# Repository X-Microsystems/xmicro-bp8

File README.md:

# XMICRO-BP8

Eight-slot [XMICRO](https://github.com/x-microsystems/xmicro-bus) backplane.

Datasheet: [XMICRO-BP8](Documentation/XMICRO-BP8.pdf)

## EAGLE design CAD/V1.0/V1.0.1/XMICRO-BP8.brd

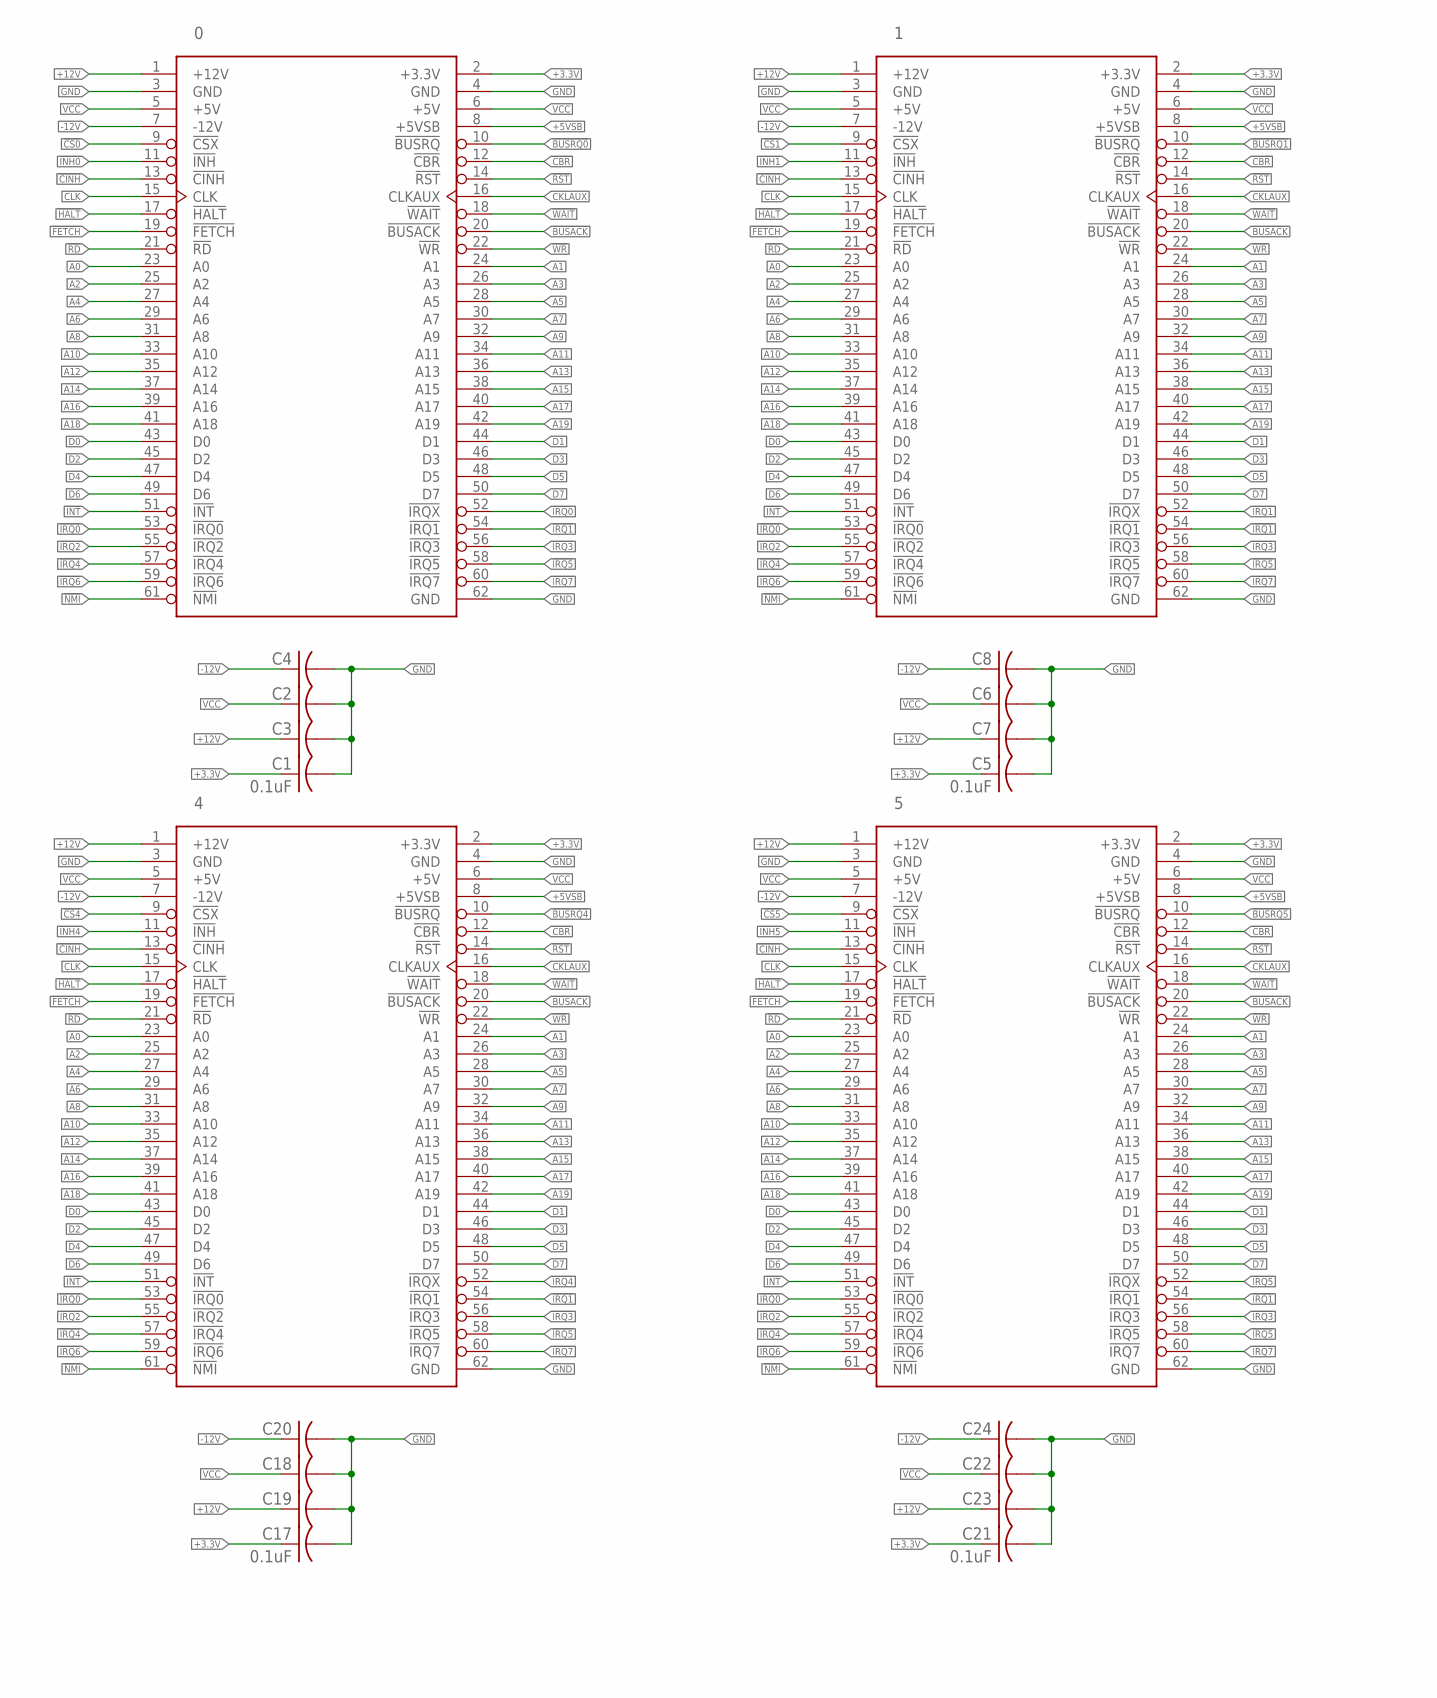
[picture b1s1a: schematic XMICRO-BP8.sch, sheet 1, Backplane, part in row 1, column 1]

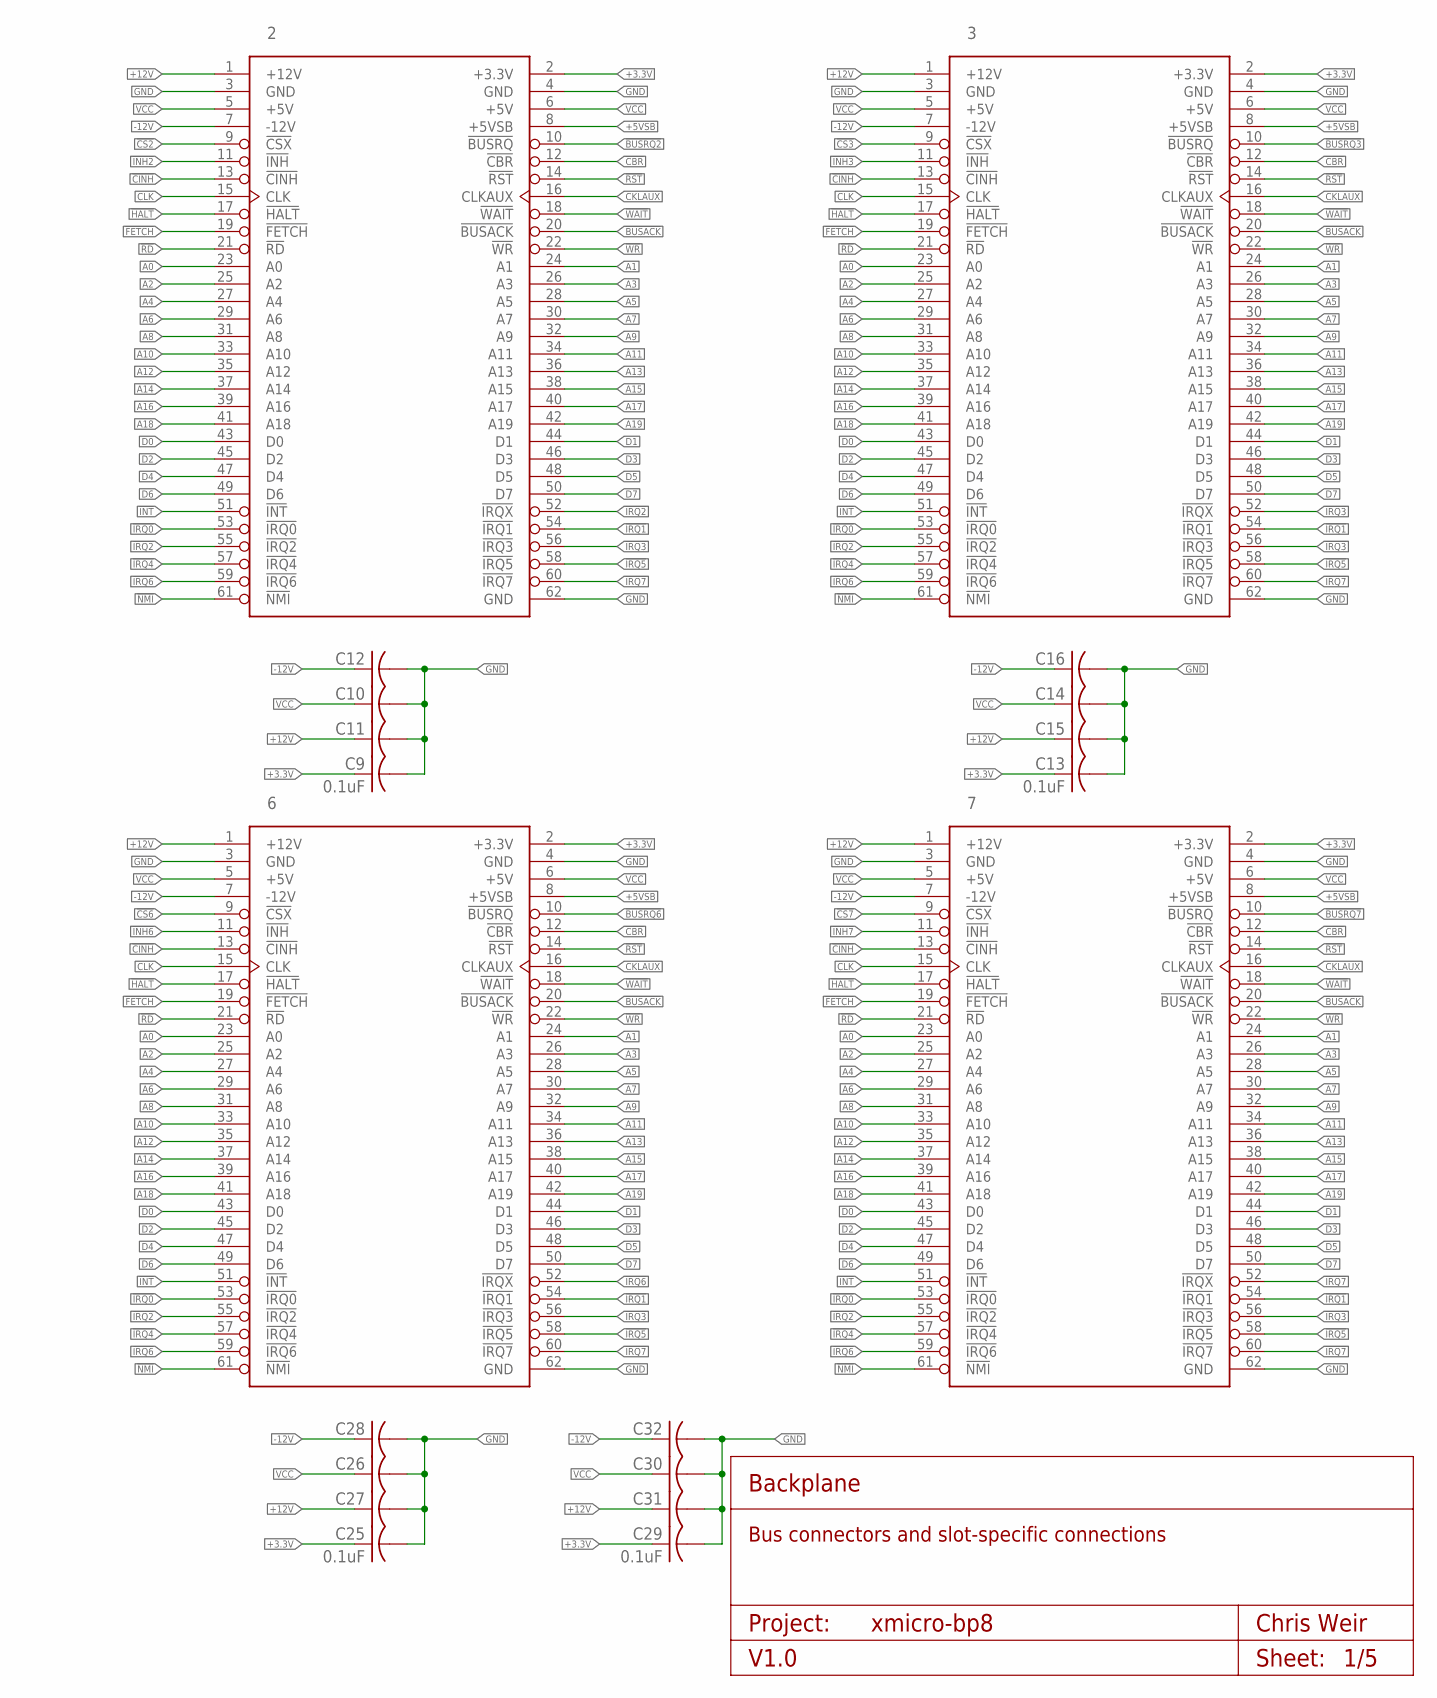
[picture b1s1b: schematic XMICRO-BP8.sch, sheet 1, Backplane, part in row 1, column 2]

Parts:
0, 1, 2, 3, 4, 5, 6, 7: XMICRO-BUS-PHYSICAL-EDGE62F; EDGE62F
C1, C2, C3, C5, C6, C7, C9, C10, C11, C13, C14, C15, C17, C18, C19, C21, C22, C23, C25, C26, C27, C29, C30, C31, C32: 0.1uF; C025-024X044
C4, C8, C12, C16, C20, C24, C28: 0.1uF; C050-024X044

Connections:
!BUSACK: 0.20 (!BUSACK), 1.20 (!BUSACK), 2.20 (!BUSACK), 3.20 (!BUSACK), 4.20 (!BUSACK), 5.20 (!BUSACK), 6.20 (!BUSACK), 7.20 (!BUSACK); also elsewhere on the board
!BUSRQ0: 0.10 (!BUSRQ); also elsewhere on the board
!BUSRQ1: 1.10 (!BUSRQ); also elsewhere on the board
!BUSRQ2: 2.10 (!BUSRQ); also elsewhere on the board
!BUSRQ3: 3.10 (!BUSRQ); also elsewhere on the board
!BUSRQ4: 4.10 (!BUSRQ); also elsewhere on the board
!BUSRQ5: 5.10 (!BUSRQ); also elsewhere on the board
!BUSRQ6: 6.10 (!BUSRQ); also elsewhere on the board
!BUSRQ7: 7.10 (!BUSRQ); also elsewhere on the board
!CBR: 0.12 (!CBR), 1.12 (!CBR), 2.12 (!CBR), 3.12 (!CBR), 4.12 (!CBR), 5.12 (!CBR), 6.12 (!CBR), 7.12 (!CBR); also elsewhere on the board
!CINH: 0.13 (!CINH), 1.13 (!CINH), 2.13 (!CINH), 3.13 (!CINH), 4.13 (!CINH), 5.13 (!CINH), 6.13 (!CINH), 7.13 (!CINH); also elsewhere on the board
!CS0: 0.9 (!CSX); also elsewhere on the board
!CS1: 1.9 (!CSX); also elsewhere on the board
!CS2: 2.9 (!CSX); also elsewhere on the board
!CS3: 3.9 (!CSX); also elsewhere on the board
!CS4: 4.9 (!CSX); also elsewhere on the board
!CS5: 5.9 (!CSX); also elsewhere on the board
!CS6: 6.9 (!CSX); also elsewhere on the board
!CS7: 7.9 (!CSX); also elsewhere on the board
!FETCH: 0.19 (!FETCH), 1.19 (!FETCH), 2.19 (!FETCH), 3.19 (!FETCH), 4.19 (!FETCH), 5.19 (!FETCH), 6.19 (!FETCH), 7.19 (!FETCH); also elsewhere on the board
!HALT: 0.17 (!HALT), 1.17 (!HALT), 2.17 (!HALT), 3.17 (!HALT), 4.17 (!HALT), 5.17 (!HALT), 6.17 (!HALT), 7.17 (!HALT); also elsewhere on the board
!INH0: 0.11 (!INH); also elsewhere on the board
!INH1: 1.11 (!INH); also elsewhere on the board
!INH2: 2.11 (!INH); also elsewhere on the board
!INH3: 3.11 (!INH); also elsewhere on the board
!INH4: 4.11 (!INH); also elsewhere on the board
!INH5: 5.11 (!INH); also elsewhere on the board
!INH6: 6.11 (!INH); also elsewhere on the board
!INH7: 7.11 (!INH); also elsewhere on the board
!INT: 0.51 (!INT), 1.51 (!INT), 2.51 (!INT), 3.51 (!INT), 4.51 (!INT), 5.51 (!INT), 6.51 (!INT), 7.51 (!INT); also elsewhere on the board
!IRQ0: 0.52 (!IRQX), 0.53 (!IRQ0), 1.53 (!IRQ0), 2.53 (!IRQ0), 3.53 (!IRQ0), 4.53 (!IRQ0), 5.53 (!IRQ0), 6.53 (!IRQ0), 7.53 (!IRQ0); also elsewhere on the board
!IRQ1: 0.54 (!IRQ1), 1.52 (!IRQX), 1.54 (!IRQ1), 2.54 (!IRQ1), 3.54 (!IRQ1), 4.54 (!IRQ1), 5.54 (!IRQ1), 6.54 (!IRQ1), 7.54 (!IRQ1); also elsewhere on the board
!IRQ2: 0.55 (!IRQ2), 1.55 (!IRQ2), 2.52 (!IRQX), 2.55 (!IRQ2), 3.55 (!IRQ2), 4.55 (!IRQ2), 5.55 (!IRQ2), 6.55 (!IRQ2), 7.55 (!IRQ2); also elsewhere on the board
!IRQ3: 0.56 (!IRQ3), 1.56 (!IRQ3), 2.56 (!IRQ3), 3.52 (!IRQX), 3.56 (!IRQ3), 4.56 (!IRQ3), 5.56 (!IRQ3), 6.56 (!IRQ3), 7.56 (!IRQ3); also elsewhere on the board
!IRQ4: 0.57 (!IRQ4), 1.57 (!IRQ4), 2.57 (!IRQ4), 3.57 (!IRQ4), 4.52 (!IRQX), 4.57 (!IRQ4), 5.57 (!IRQ4), 6.57 (!IRQ4), 7.57 (!IRQ4); also elsewhere on the board
!IRQ5: 0.58 (!IRQ5), 1.58 (!IRQ5), 2.58 (!IRQ5), 3.58 (!IRQ5), 4.58 (!IRQ5), 5.52 (!IRQX), 5.58 (!IRQ5), 6.58 (!IRQ5), 7.58 (!IRQ5); also elsewhere on the board
!IRQ6: 0.59 (!IRQ6), 1.59 (!IRQ6), 2.59 (!IRQ6), 3.59 (!IRQ6), 4.59 (!IRQ6), 5.59 (!IRQ6), 6.52 (!IRQX), 6.59 (!IRQ6), 7.59 (!IRQ6); also elsewhere on the board
!IRQ7: 0.60 (!IRQ7), 1.60 (!IRQ7), 2.60 (!IRQ7), 3.60 (!IRQ7), 4.60 (!IRQ7), 5.60 (!IRQ7), 6.60 (!IRQ7), 7.52 (!IRQX), 7.60 (!IRQ7); also elsewhere on the board
!NMI: 0.61 (!NMI), 1.61 (!NMI), 2.61 (!NMI), 3.61 (!NMI), 4.61 (!NMI), 5.61 (!NMI), 6.61 (!NMI), 7.61 (!NMI); also elsewhere on the board
!RD: 0.21 (!RD), 1.21 (!RD), 2.21 (!RD), 3.21 (!RD), 4.21 (!RD), 5.21 (!RD), 6.21 (!RD), 7.21 (!RD); also elsewhere on the board
!RST: 0.14 (!RST), 1.14 (!RST), 2.14 (!RST), 3.14 (!RST), 4.14 (!RST), 5.14 (!RST), 6.14 (!RST), 7.14 (!RST); also elsewhere on the board
!WAIT: 0.18 (!WAIT), 1.18 (!WAIT), 2.18 (!WAIT), 3.18 (!WAIT), 4.18 (!WAIT), 5.18 (!WAIT), 6.18 (!WAIT), 7.18 (!WAIT); also elsewhere on the board
!WR: 0.22 (!WR), 1.22 (!WR), 2.22 (!WR), 3.22 (!WR), 4.22 (!WR), 5.22 (!WR), 6.22 (!WR), 7.22 (!WR); also elsewhere on the board
+3.3V: 0.2 (+3.3V), 1.2 (+3.3V), 2.2 (+3.3V), 3.2 (+3.3V), 4.2 (+3.3V), 5.2 (+3.3V), 6.2 (+3.3V), 7.2 (+3.3V), C1.1, C5.1, C9.1, C13.1, C17.1, C21.1, C25.1, C29.1; also elsewhere on the board
+5VSB: 0.8 (+5VSB), 1.8 (+5VSB), 2.8 (+5VSB), 3.8 (+5VSB), 4.8 (+5VSB), 5.8 (+5VSB), 6.8 (+5VSB), 7.8 (+5VSB); also elsewhere on the board
+12V: 0.1 (+12V), 1.1 (+12V), 2.1 (+12V), 3.1 (+12V), 4.1 (+12V), 5.1 (+12V), 6.1 (+12V), 7.1 (+12V), C3.1, C7.1, C11.1, C15.1, C19.1, C23.1, C27.1, C31.1; also elsewhere on the board
A0: 0.23 (A0), 1.23 (A0), 2.23 (A0), 3.23 (A0), 4.23 (A0), 5.23 (A0), 6.23 (A0), 7.23 (A0); also elsewhere on the board
A1: 0.24 (A1), 1.24 (A1), 2.24 (A1), 3.24 (A1), 4.24 (A1), 5.24 (A1), 6.24 (A1), 7.24 (A1); also elsewhere on the board
A2: 0.25 (A2), 1.25 (A2), 2.25 (A2), 3.25 (A2), 4.25 (A2), 5.25 (A2), 6.25 (A2), 7.25 (A2); also elsewhere on the board
A3: 0.26 (A3), 1.26 (A3), 2.26 (A3), 3.26 (A3), 4.26 (A3), 5.26 (A3), 6.26 (A3), 7.26 (A3); also elsewhere on the board
A4: 0.27 (A4), 1.27 (A4), 2.27 (A4), 3.27 (A4), 4.27 (A4), 5.27 (A4), 6.27 (A4), 7.27 (A4); also elsewhere on the board
A5: 0.28 (A5), 1.28 (A5), 2.28 (A5), 3.28 (A5), 4.28 (A5), 5.28 (A5), 6.28 (A5), 7.28 (A5); also elsewhere on the board
A6: 0.29 (A6), 1.29 (A6), 2.29 (A6), 3.29 (A6), 4.29 (A6), 5.29 (A6), 6.29 (A6), 7.29 (A6); also elsewhere on the board
A7: 0.30 (A7), 1.30 (A7), 2.30 (A7), 3.30 (A7), 4.30 (A7), 5.30 (A7), 6.30 (A7), 7.30 (A7); also elsewhere on the board
A8: 0.31 (A8), 1.31 (A8), 2.31 (A8), 3.31 (A8), 4.31 (A8), 5.31 (A8), 6.31 (A8), 7.31 (A8); also elsewhere on the board
A9: 0.32 (A9), 1.32 (A9), 2.32 (A9), 3.32 (A9), 4.32 (A9), 5.32 (A9), 6.32 (A9), 7.32 (A9); also elsewhere on the board
A10: 0.33 (A10), 1.33 (A10), 2.33 (A10), 3.33 (A10), 4.33 (A10), 5.33 (A10), 6.33 (A10), 7.33 (A10); also elsewhere on the board
A11: 0.34 (A11), 1.34 (A11), 2.34 (A11), 3.34 (A11), 4.34 (A11), 5.34 (A11), 6.34 (A11), 7.34 (A11); also elsewhere on the board
A12: 0.35 (A12), 1.35 (A12), 2.35 (A12), 3.35 (A12), 4.35 (A12), 5.35 (A12), 6.35 (A12), 7.35 (A12); also elsewhere on the board
A13: 0.36 (A13), 1.36 (A13), 2.36 (A13), 3.36 (A13), 4.36 (A13), 5.36 (A13), 6.36 (A13), 7.36 (A13); also elsewhere on the board
A14: 0.37 (A14), 1.37 (A14), 2.37 (A14), 3.37 (A14), 4.37 (A14), 5.37 (A14), 6.37 (A14), 7.37 (A14); also elsewhere on the board
A15: 0.38 (A15), 1.38 (A15), 2.38 (A15), 3.38 (A15), 4.38 (A15), 5.38 (A15), 6.38 (A15), 7.38 (A15); also elsewhere on the board
A16: 0.39 (A16), 1.39 (A16), 2.39 (A16), 3.39 (A16), 4.39 (A16), 5.39 (A16), 6.39 (A16), 7.39 (A16); also elsewhere on the board
A17: 0.40 (A17), 1.40 (A17), 2.40 (A17), 3.40 (A17), 4.40 (A17), 5.40 (A17), 6.40 (A17), 7.40 (A17); also elsewhere on the board
A18: 0.41 (A18), 1.41 (A18), 2.41 (A18), 3.41 (A18), 4.41 (A18), 5.41 (A18), 6.41 (A18), 7.41 (A18); also elsewhere on the board
A19: 0.42 (A19), 1.42 (A19), 2.42 (A19), 3.42 (A19), 4.42 (A19), 5.42 (A19), 6.42 (A19), 7.42 (A19); also elsewhere on the board
CKLAUX: 0.16 (CLKAUX), 1.16 (CLKAUX), 2.16 (CLKAUX), 3.16 (CLKAUX), 4.16 (CLKAUX), 5.16 (CLKAUX), 6.16 (CLKAUX), 7.16 (CLKAUX); also elsewhere on the board
CLK: 0.15 (CLK), 1.15 (CLK), 2.15 (CLK), 3.15 (CLK), 4.15 (CLK), 5.15 (CLK), 6.15 (CLK), 7.15 (CLK); also elsewhere on the board
D0: 0.43 (D0), 1.43 (D0), 2.43 (D0), 3.43 (D0), 4.43 (D0), 5.43 (D0), 6.43 (D0), 7.43 (D0); also elsewhere on the board
D1: 0.44 (D1), 1.44 (D1), 2.44 (D1), 3.44 (D1), 4.44 (D1), 5.44 (D1), 6.44 (D1), 7.44 (D1); also elsewhere on the board
D2: 0.45 (D2), 1.45 (D2), 2.45 (D2), 3.45 (D2), 4.45 (D2), 5.45 (D2), 6.45 (D2), 7.45 (D2); also elsewhere on the board
D3: 0.46 (D3), 1.46 (D3), 2.46 (D3), 3.46 (D3), 4.46 (D3), 5.46 (D3), 6.46 (D3), 7.46 (D3); also elsewhere on the board
D4: 0.47 (D4), 1.47 (D4), 2.47 (D4), 3.47 (D4), 4.47 (D4), 5.47 (D4), 6.47 (D4), 7.47 (D4); also elsewhere on the board
D5: 0.48 (D5), 1.48 (D5), 2.48 (D5), 3.48 (D5), 4.48 (D5), 5.48 (D5), 6.48 (D5), 7.48 (D5); also elsewhere on the board
D6: 0.49 (D6), 1.49 (D6), 2.49 (D6), 3.49 (D6), 4.49 (D6), 5.49 (D6), 6.49 (D6), 7.49 (D6); also elsewhere on the board
D7: 0.50 (D7), 1.50 (D7), 2.50 (D7), 3.50 (D7), 4.50 (D7), 5.50 (D7), 6.50 (D7), 7.50 (D7); also elsewhere on the board
VCC: 0.5 (+5V), 0.6 (+5V), 1.5 (+5V), 1.6 (+5V), 2.5 (+5V), 2.6 (+5V), 3.5 (+5V), 3.6 (+5V), 4.5 (+5V), 4.6 (+5V), 5.5 (+5V), 5.6 (+5V), 6.5 (+5V), 6.6 (+5V), 7.5 (+5V), 7.6 (+5V), C2.1, C6.1, C10.1, C14.1, C18.1, C22.1, C26.1, C30.1; also elsewhere on the board

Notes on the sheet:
Backplane
Bus connectors and slot-specific connections
Project:
V1.0
Chris Weir
Sheet:

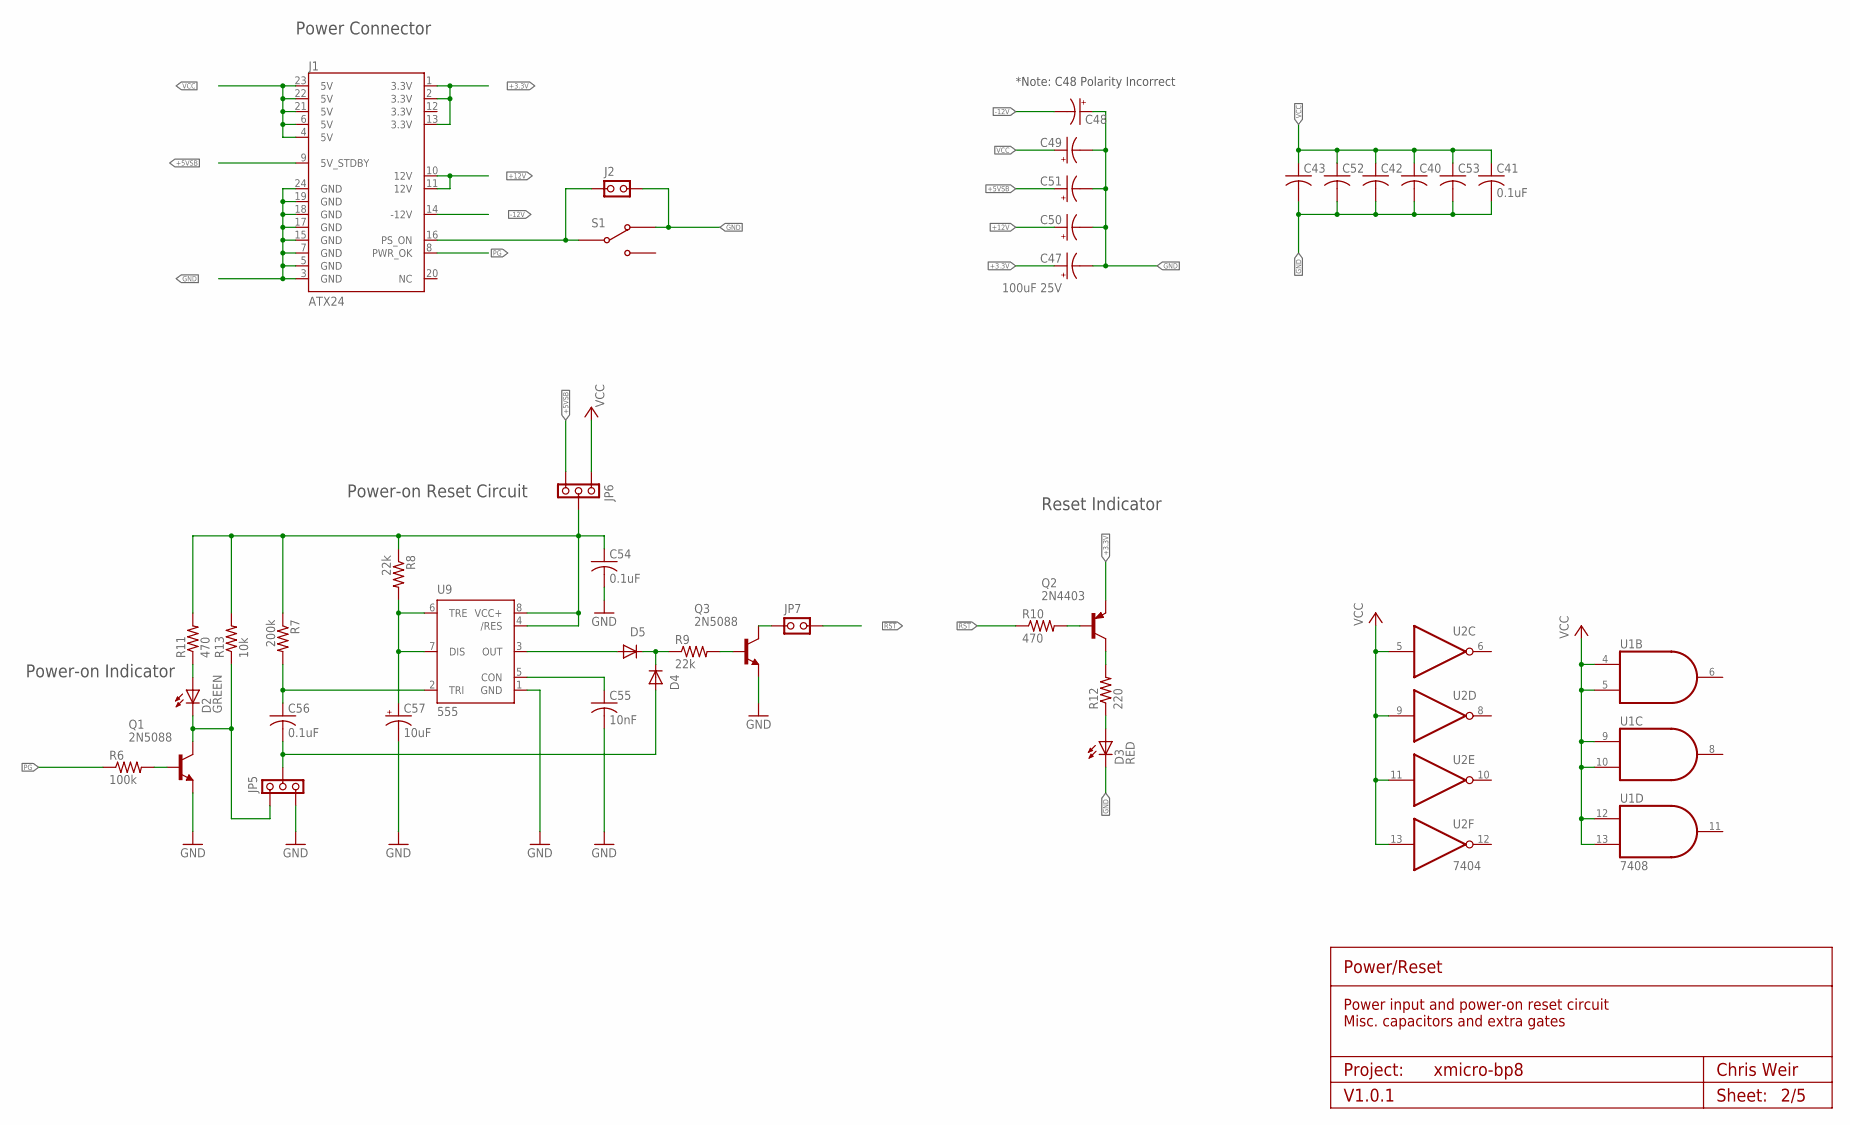
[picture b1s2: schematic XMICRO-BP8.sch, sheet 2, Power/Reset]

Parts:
C40, C41, C42, C43, C52, C53, C54, C56: 0.1uF; C025-024X044
C47, C50: 100uF 25V; C-10-5
C48, C49, C51: 220uF 10V; C-10-5
C55: 10nF; C025-024X044
C57: 10uF; E2,5-7
D2: GREEN; LED5MM
D3: RED; LED5MM
D4, D5: 1N4148DO35-7; DO35-7
J1: ATX24
J2: PINHD-1X2THRU; 1X02
JP5, JP6: PINHD1X3THRU; 1X03
JP7: PINHD-1X2THRU; 1X02
Q1, Q3: 2N5088; TO92
Q2: 2N4403; TO92
R6: 100k; 0207/10
R7: 200k; 0207/10
R8, R9: 22k; 0207/10
R10, R11: 470; 0207/10
R12: 220; 0207/10
R13: 10k; 0207/10
S1: SPDTT411013; T411013
U1: 7408; DIL14
U2: 7404; DIL14
U9: 555; DIL-08

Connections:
!RST: JP7.2, R10.1; also elsewhere on the board
+3.3V: C47.+, J1.1 (3.3V), J1.2 (3.3V), J1.13 (3.3V), Q2.1 (E); also elsewhere on the board
+5VSB: C51.+, J1.9 (5V_STDBY), JP6.3; also elsewhere on the board
+12V: C50.+, J1.10 (12V), J1.11 (12V); also elsewhere on the board
unnamed: D2.K (C), JP5.1, Q1.3 (C), R13.1
unnamed: Q2.3 (C), R12.2
unnamed: Q2.2 (B), R10.2
unnamed: D5.A, U9.3 (OUT)
unnamed: JP7.1, Q3.3 (C)
unnamed: D3.A, R12.1
unnamed: J1.16 (PS_ON), J2.1, S1.P$2
unnamed: Q1.2 (B), R6.2
unnamed: D2.A, R11.1
unnamed: C55.1, U9.5 (CON)
unnamed: D4.C, D5.C, R9.1
unnamed: C54.1, JP6.2, R7.1, R8.1, R11.2, R13.2, U9.4 (/RES), U9.8 (VCC+)
unnamed: C56.2, D4.A, JP5.2
unnamed: Q3.2 (B), R9.2
unnamed: C56.1, R7.2, U9.2 (TRI)
unnamed: C57.+, R8.2, U9.6 (TRE), U9.7 (DIS)
PG: J1.8 (PWR_OK), R6.1
VCC: C40.1, C41.1, C42.1, C43.1, C49.+, C52.1, C53.1, J1.4 (5V), J1.6 (5V), J1.21 (5V), J1.22 (5V), J1.23 (5V), JP6.1, U1.4 (I0), U1.5 (I1), U1.9 (I0), U1.10 (I1), U1.12 (I0), U1.13 (I1), U1.14 (VCC), U2.5 (I), U2.9 (I), U2.11 (I), U2.13 (I), U2.14 (VCC); also elsewhere on the board

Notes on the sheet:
Power/Reset
Power input and power-on reset circuit Misc. capacitors and extra gates
Power Connector
Project:
V1.0.1
Chris Weir
Sheet:
*Note: C48 Polarity Incorrect
Power-on Indicator
Reset Indicator
Power-on Reset Circuit

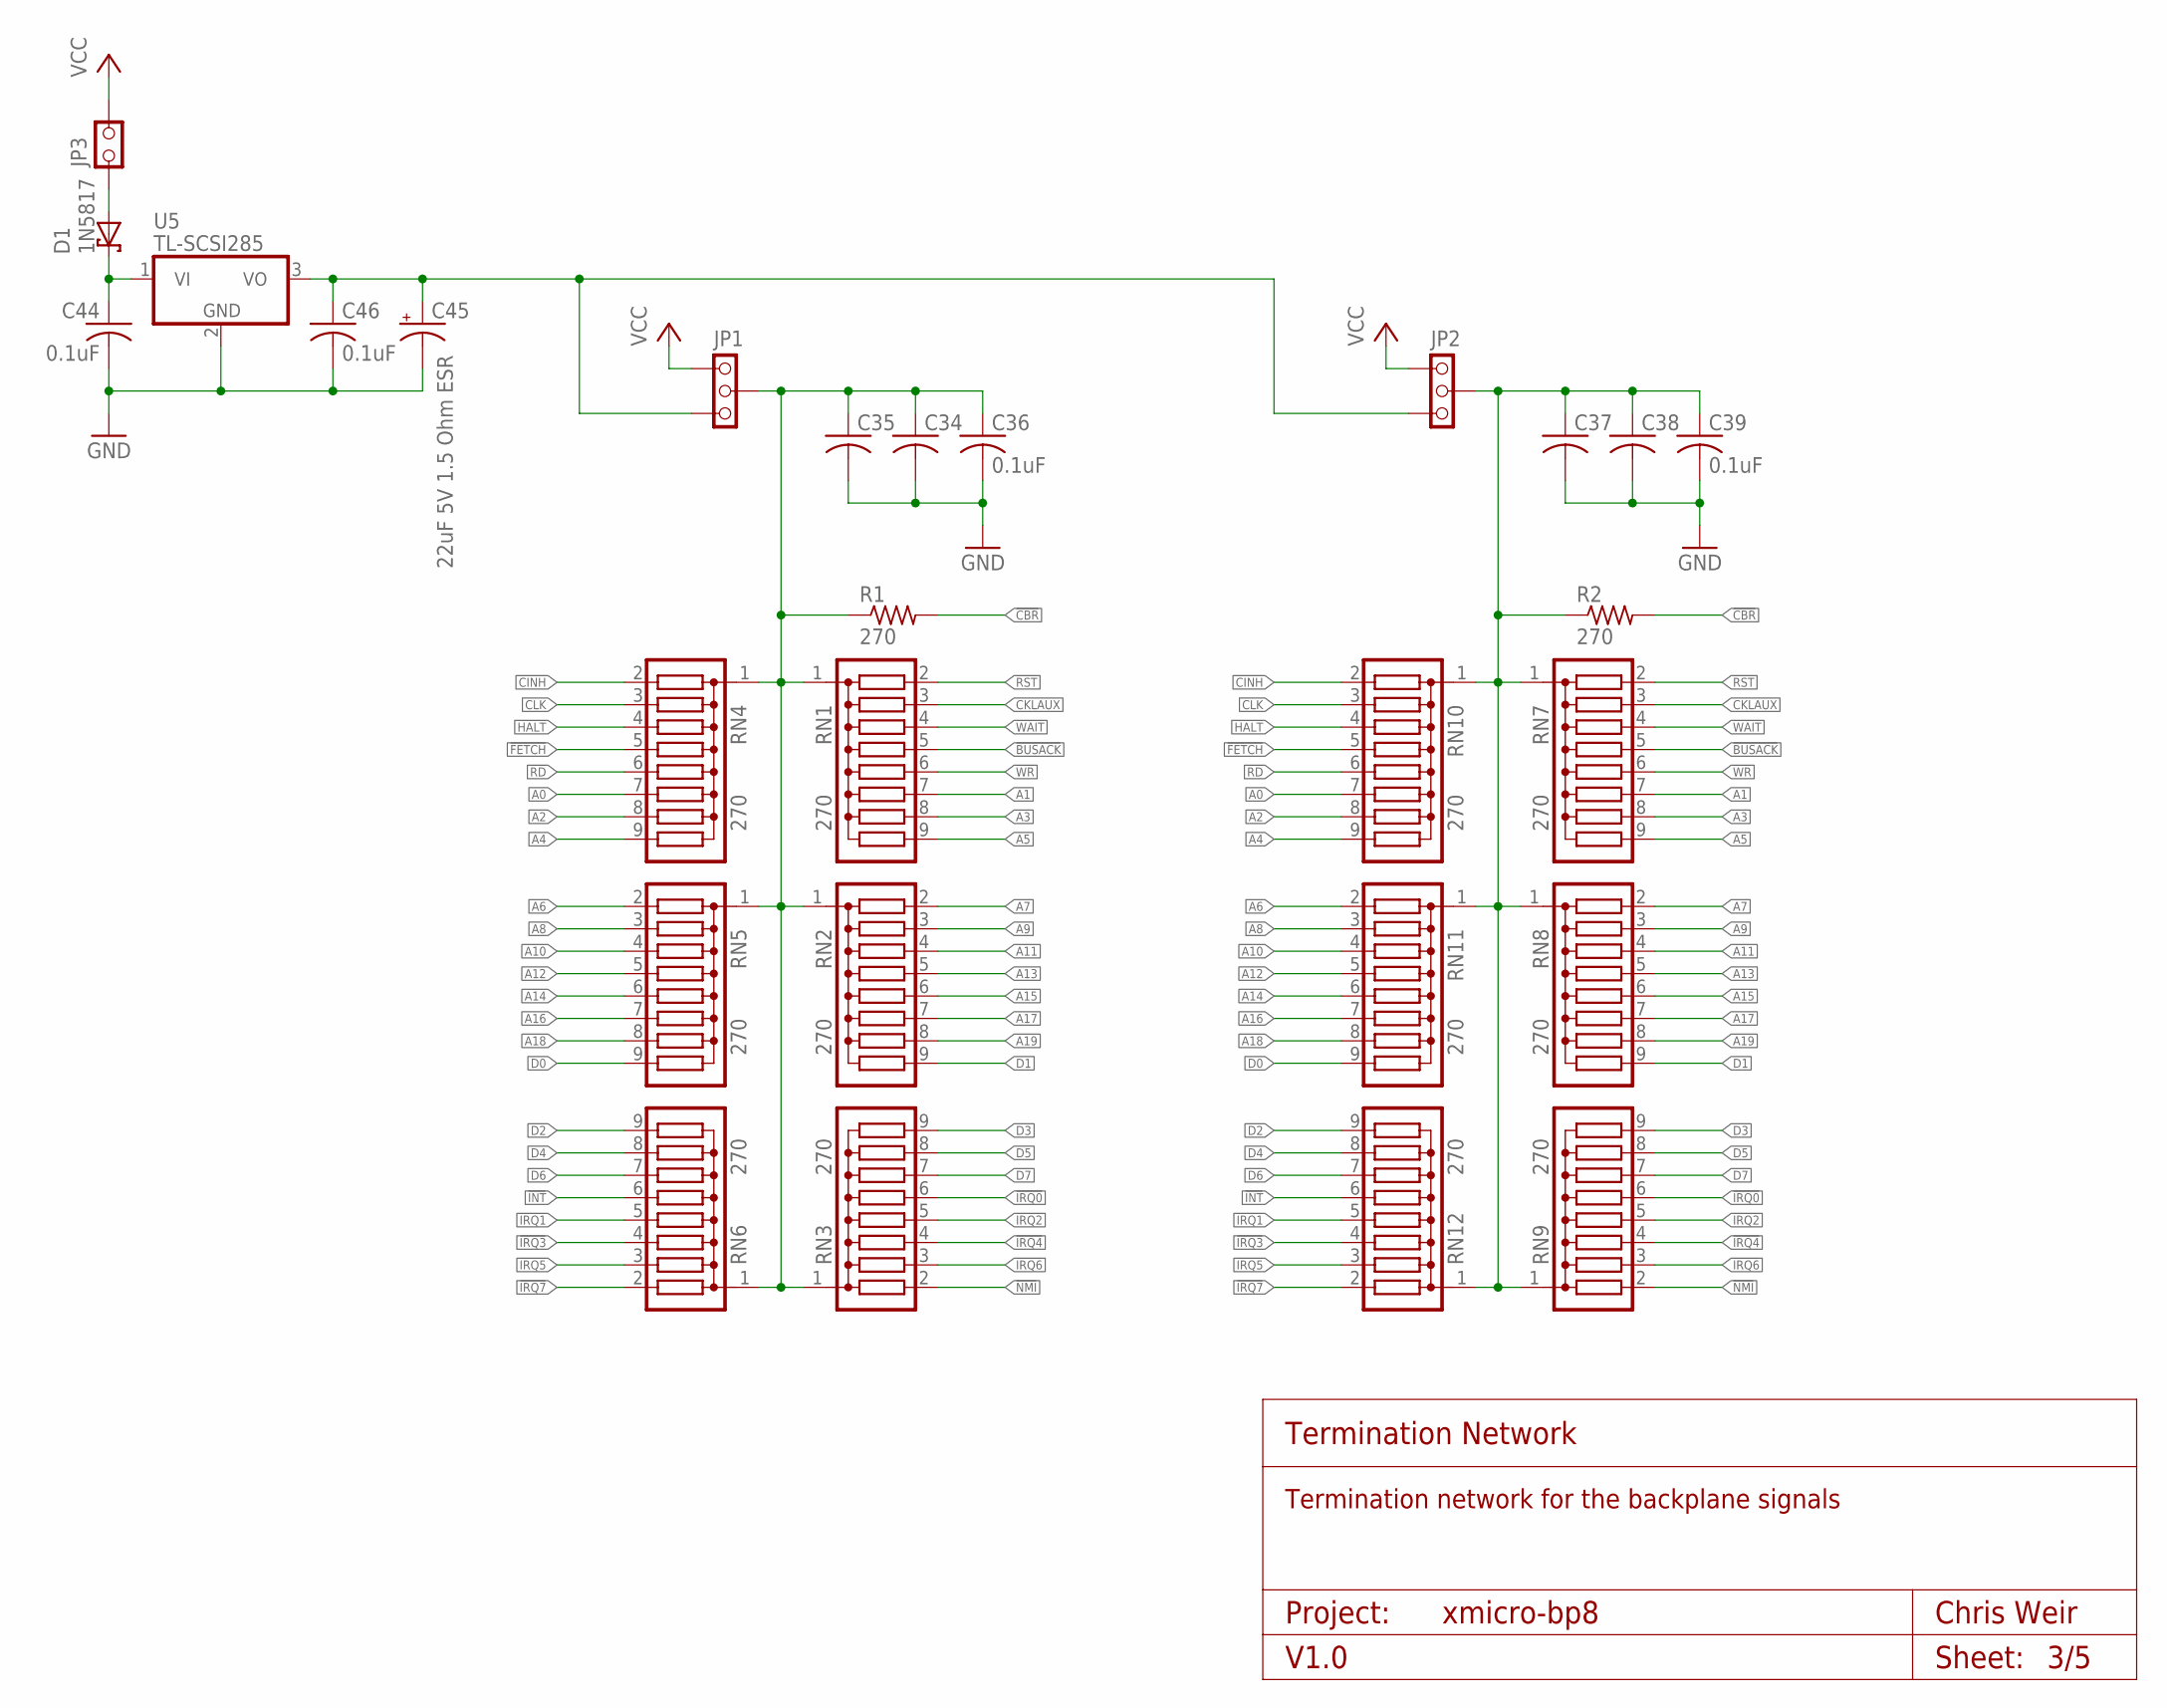
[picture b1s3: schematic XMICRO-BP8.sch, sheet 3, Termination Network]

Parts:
C34, C35, C36, C37, C38, C39, C44: 0.1uF; C025-024X044
C45: 22uF 5V 1.5 Ohm ESR; E2,5-7
C46: 0.1uF; C050-024X044
D1: 1N5817; DO41-7.6
JP1, JP2: PINHD1X3THRU; 1X03
JP3: PINHD-1X2THRU; 1X02
R1, R2: 270; 0207/10
RN1, RN2, RN3, RN4, RN5, RN6, RN7, RN8, RN9, RN10, RN11, RN12: 270; SIL9
U5: TL-SCSI285; TO220H

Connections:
!BUSACK: RN1.5, RN7.5; also elsewhere on the board
!CBR: R1.2, R2.2; also elsewhere on the board
!CINH: RN4.2, RN10.2; also elsewhere on the board
!FETCH: RN4.5, RN10.5; also elsewhere on the board
!HALT: RN4.4, RN10.4; also elsewhere on the board
!INT: RN6.6, RN12.6; also elsewhere on the board
!IRQ0: RN3.6, RN9.6; also elsewhere on the board
!IRQ1: RN6.5, RN12.5; also elsewhere on the board
!IRQ2: RN3.5, RN9.5; also elsewhere on the board
!IRQ3: RN6.4, RN12.4; also elsewhere on the board
!IRQ4: RN3.4, RN9.4; also elsewhere on the board
!IRQ5: RN6.3, RN12.3; also elsewhere on the board
!IRQ6: RN3.3, RN9.3; also elsewhere on the board
!IRQ7: RN6.2, RN12.2; also elsewhere on the board
!NMI: RN3.2, RN9.2; also elsewhere on the board
!RD: RN4.6, RN10.6; also elsewhere on the board
!RST: RN1.2, RN7.2; also elsewhere on the board
!WAIT: RN1.4, RN7.4; also elsewhere on the board
!WR: RN1.6, RN7.6; also elsewhere on the board
A0: RN4.7, RN10.7; also elsewhere on the board
A1: RN1.7, RN7.7; also elsewhere on the board
A2: RN4.8, RN10.8; also elsewhere on the board
A3: RN1.8, RN7.8; also elsewhere on the board
A4: RN4.9, RN10.9; also elsewhere on the board
A5: RN1.9, RN7.9; also elsewhere on the board
A6: RN5.2, RN11.2; also elsewhere on the board
A7: RN2.2, RN8.2; also elsewhere on the board
A8: RN5.3, RN11.3; also elsewhere on the board
A9: RN2.3, RN8.3; also elsewhere on the board
A10: RN5.4, RN11.4; also elsewhere on the board
A11: RN2.4, RN8.4; also elsewhere on the board
A12: RN5.5, RN11.5; also elsewhere on the board
A13: RN2.5, RN8.5; also elsewhere on the board
A14: RN5.6, RN11.6; also elsewhere on the board
A15: RN2.6, RN8.6; also elsewhere on the board
A16: RN5.7, RN11.7; also elsewhere on the board
A17: RN2.7, RN8.7; also elsewhere on the board
A18: RN5.8, RN11.8; also elsewhere on the board
A19: RN2.8, RN8.8; also elsewhere on the board
CKLAUX: RN1.3, RN7.3; also elsewhere on the board
CLK: RN4.3, RN10.3; also elsewhere on the board
D0: RN5.9, RN11.9; also elsewhere on the board
D1: RN2.9, RN8.9; also elsewhere on the board
D2: RN6.9, RN12.9; also elsewhere on the board
D3: RN3.9, RN9.9; also elsewhere on the board
D4: RN6.8, RN12.8; also elsewhere on the board
D5: RN3.8, RN9.8; also elsewhere on the board
D6: RN6.7, RN12.7; also elsewhere on the board
D7: RN3.7, RN9.7; also elsewhere on the board
unnamed: C45.+, C46.1, JP1.3, JP2.3, U5.3 (VO)
unnamed: D1.A, JP3.1
unnamed: C44.1, D1.C, U5.1 (VI)
unnamed: C37.1, C38.1, C39.1, JP2.2, R2.1, RN7.1, RN8.1, RN9.1, RN10.1, RN11.1, RN12.1
unnamed: C34.1, C35.1, C36.1, JP1.2, R1.1, RN1.1, RN2.1, RN3.1, RN4.1, RN5.1, RN6.1
VCC: JP1.1, JP2.1, JP3.2; also elsewhere on the board

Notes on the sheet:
Termination Network
Termination network for the backplane signals
Project:
V1.0
Chris Weir
Sheet:

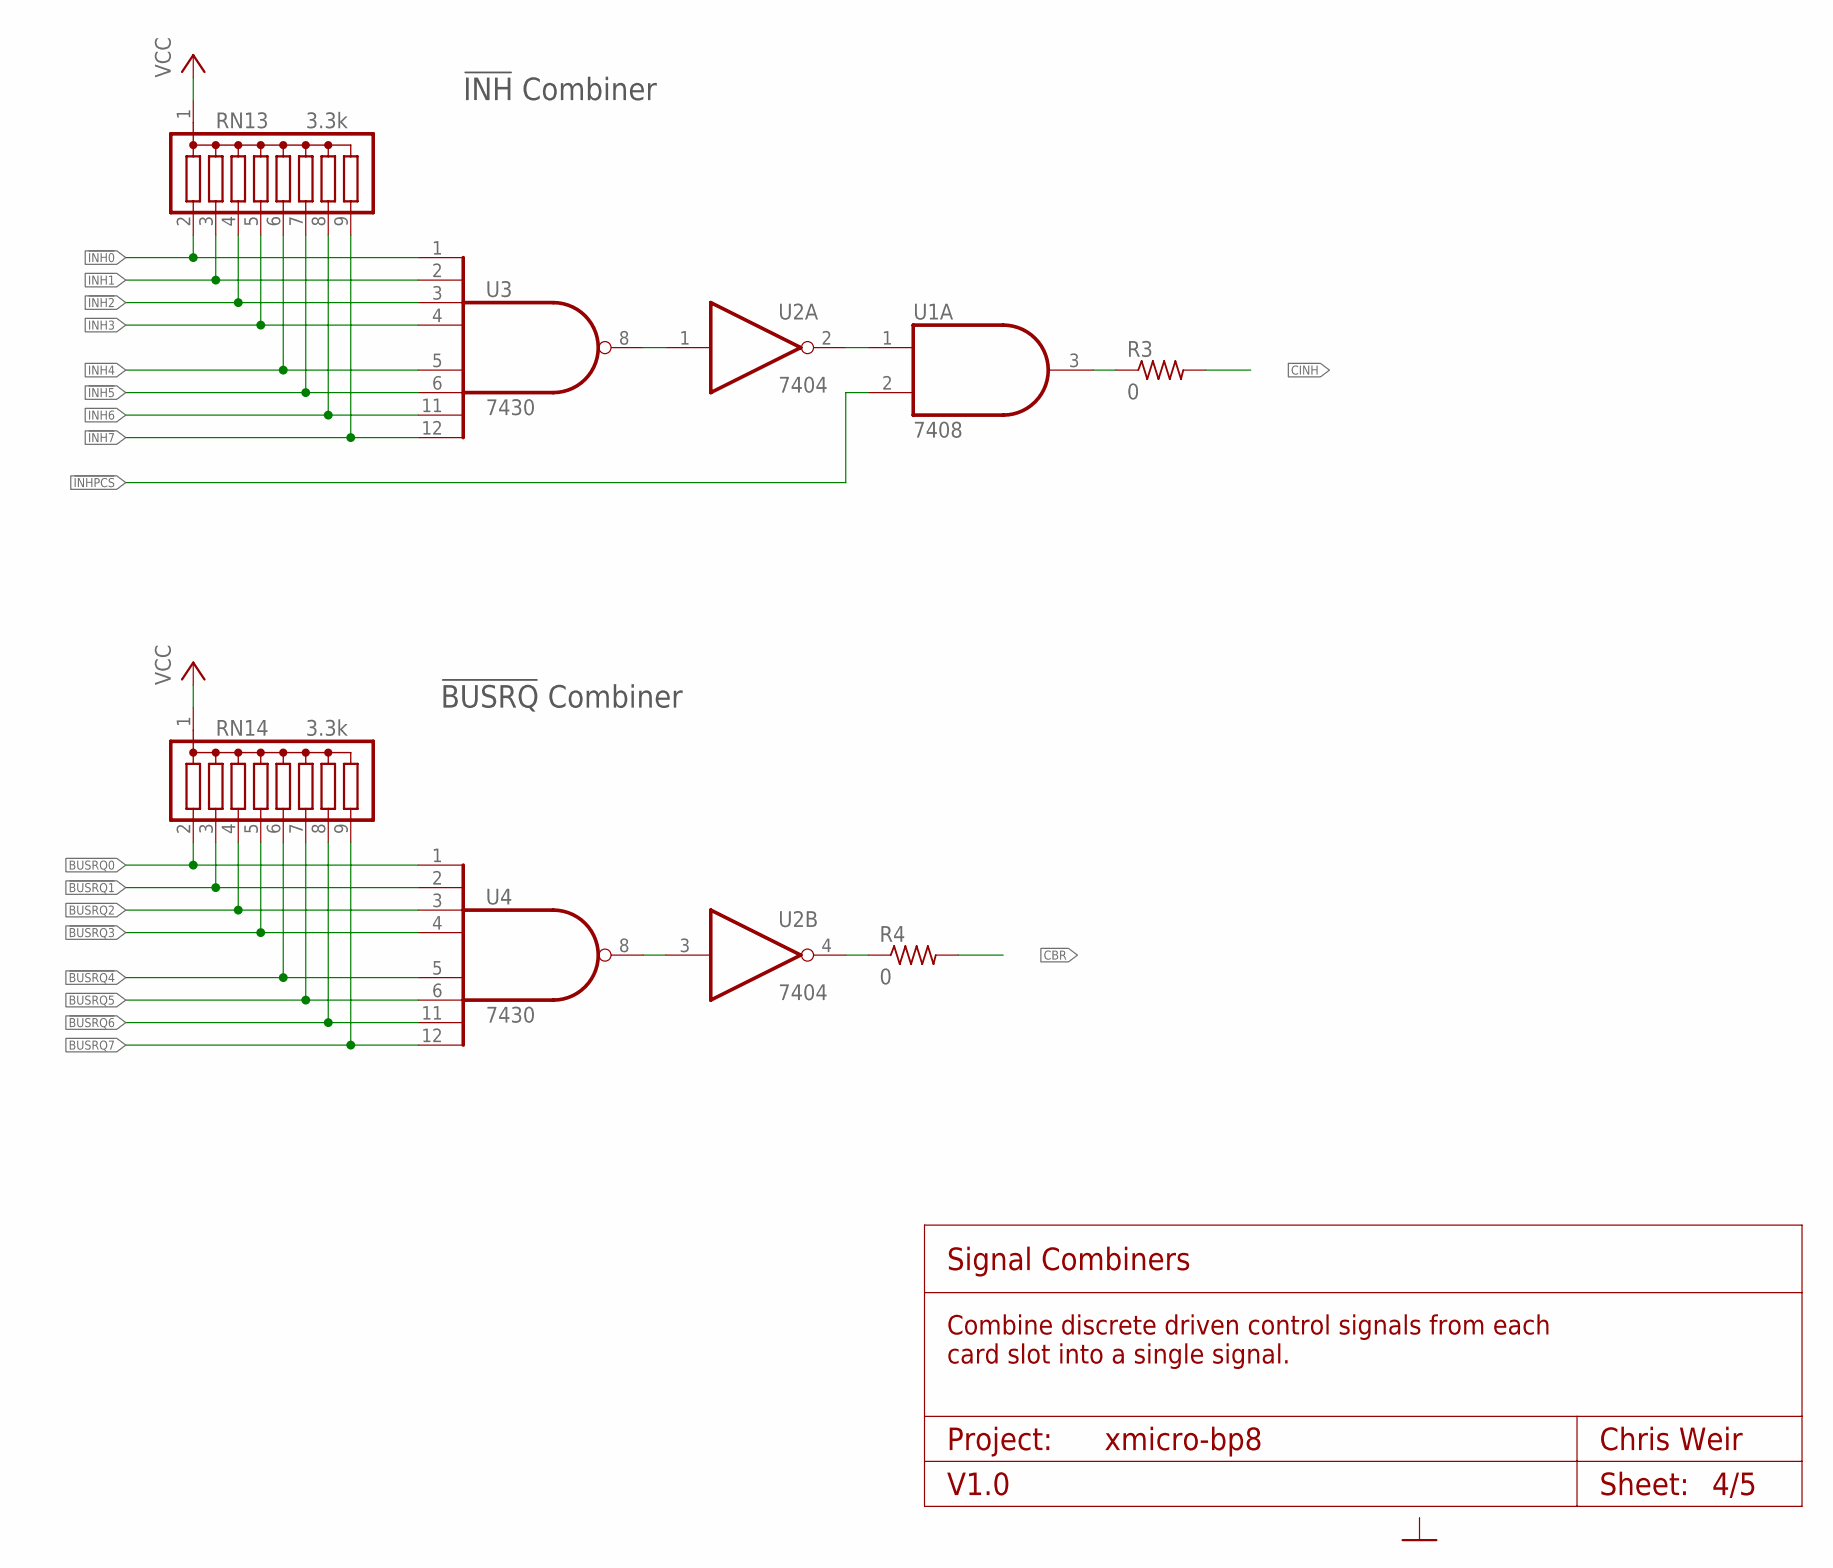
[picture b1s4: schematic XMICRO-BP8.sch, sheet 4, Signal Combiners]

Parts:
R3, R4: 0; 0207/10
RN13, RN14: 3.3k; SIL9
U1: 7408; DIL14
U2: 7404; DIL14
U3, U4: 7430; DIL14

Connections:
!BUSRQ0: RN14.2, U4.1 (I0); also elsewhere on the board
!BUSRQ1: RN14.3, U4.2 (I1); also elsewhere on the board
!BUSRQ2: RN14.4, U4.3 (I2); also elsewhere on the board
!BUSRQ3: RN14.5, U4.4 (I3); also elsewhere on the board
!BUSRQ4: RN14.6, U4.5 (I4); also elsewhere on the board
!BUSRQ5: RN14.7, U4.6 (I5); also elsewhere on the board
!BUSRQ6: RN14.8, U4.11 (I6); also elsewhere on the board
!BUSRQ7: RN14.9, U4.12 (I7); also elsewhere on the board
!CBR: R4.2; also elsewhere on the board
!CINH: R3.2; also elsewhere on the board
!INH0: RN13.2, U3.1 (I0); also elsewhere on the board
!INH1: RN13.3, U3.2 (I1); also elsewhere on the board
!INH2: RN13.4, U3.3 (I2); also elsewhere on the board
!INH3: RN13.5, U3.4 (I3); also elsewhere on the board
!INH4: RN13.6, U3.5 (I4); also elsewhere on the board
!INH5: RN13.7, U3.6 (I5); also elsewhere on the board
!INH6: RN13.8, U3.11 (I6); also elsewhere on the board
!INH7: RN13.9, U3.12 (I7); also elsewhere on the board
!INHPCS: U1.2 (I1); also elsewhere on the board
unnamed: U2.1 (I), U3.8 (O)
unnamed: U1.1 (I0), U2.2 (O)
unnamed: U2.3 (I), U4.8 (O)
unnamed: R4.1, U2.4 (O)
unnamed: R3.1, U1.3 (O)
VCC: RN13.1, RN14.1, U1.14 (VCC), U2.14 (VCC), U3.14 (VCC), U4.14 (VCC); also elsewhere on the board

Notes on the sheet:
!INH! Combiner
!BUSRQ! Combiner
Signal Combiners
Combine discrete driven control signals from each card slot into a single signal.
Project:
V1.0
Chris Weir
Sheet:
